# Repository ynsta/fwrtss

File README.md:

fwrtss
======

[FWRTSS](https://www.ynsta.org/fwrtss/doc/html/fwrtss.html) is an open source hardware and software project of a temperature controlled soldering station designed to be used with Weller RT soldering tips.

The majority of the software used to build and debug this project are also open source:

 - KiCad (5126) for PCB design with the [amazing new interactive router from CERN team](http://www.ohwr.org/projects/cern-kicad/wiki/WorkPackages).

 - ARM cross GCC (4.8.3) & binutils,

 - GDB cross, stlink,

 - dfu-util,

 - python, pyside, pyqtgraph,

 - scons, make

 - asciidoc,

 - emacs,

 - ...

The main goal of this project was to teach myself some new stuffs as it is my first real project with a stm32 MCU and also my first surface mount PCB project with 0.5mm pitch components.
Disclaimer

# Warning
 
**A SOLDERING STATION IS A DANGEROUS TOOL**

FWRTSS open source software and hardware are provided "as is" and any express or implied warranties, including, but not limited to, the implied warranties of merchantability and fitness for a particular purpose are disclaimed. in no event shall Stany MARCEL be liable for any direct, indirect, incidental, special, exemplary, or consequential damages (including, but not limited to, procurement of substitute goods or services; loss of use, data, or profits; or business interruption) however caused and on any theory of liability, whether in contract, strict liability, or tort (including negligence or otherwise) arising in any way out of the use of this tool (in whole or in part), even if advised of the possibility of such damage.

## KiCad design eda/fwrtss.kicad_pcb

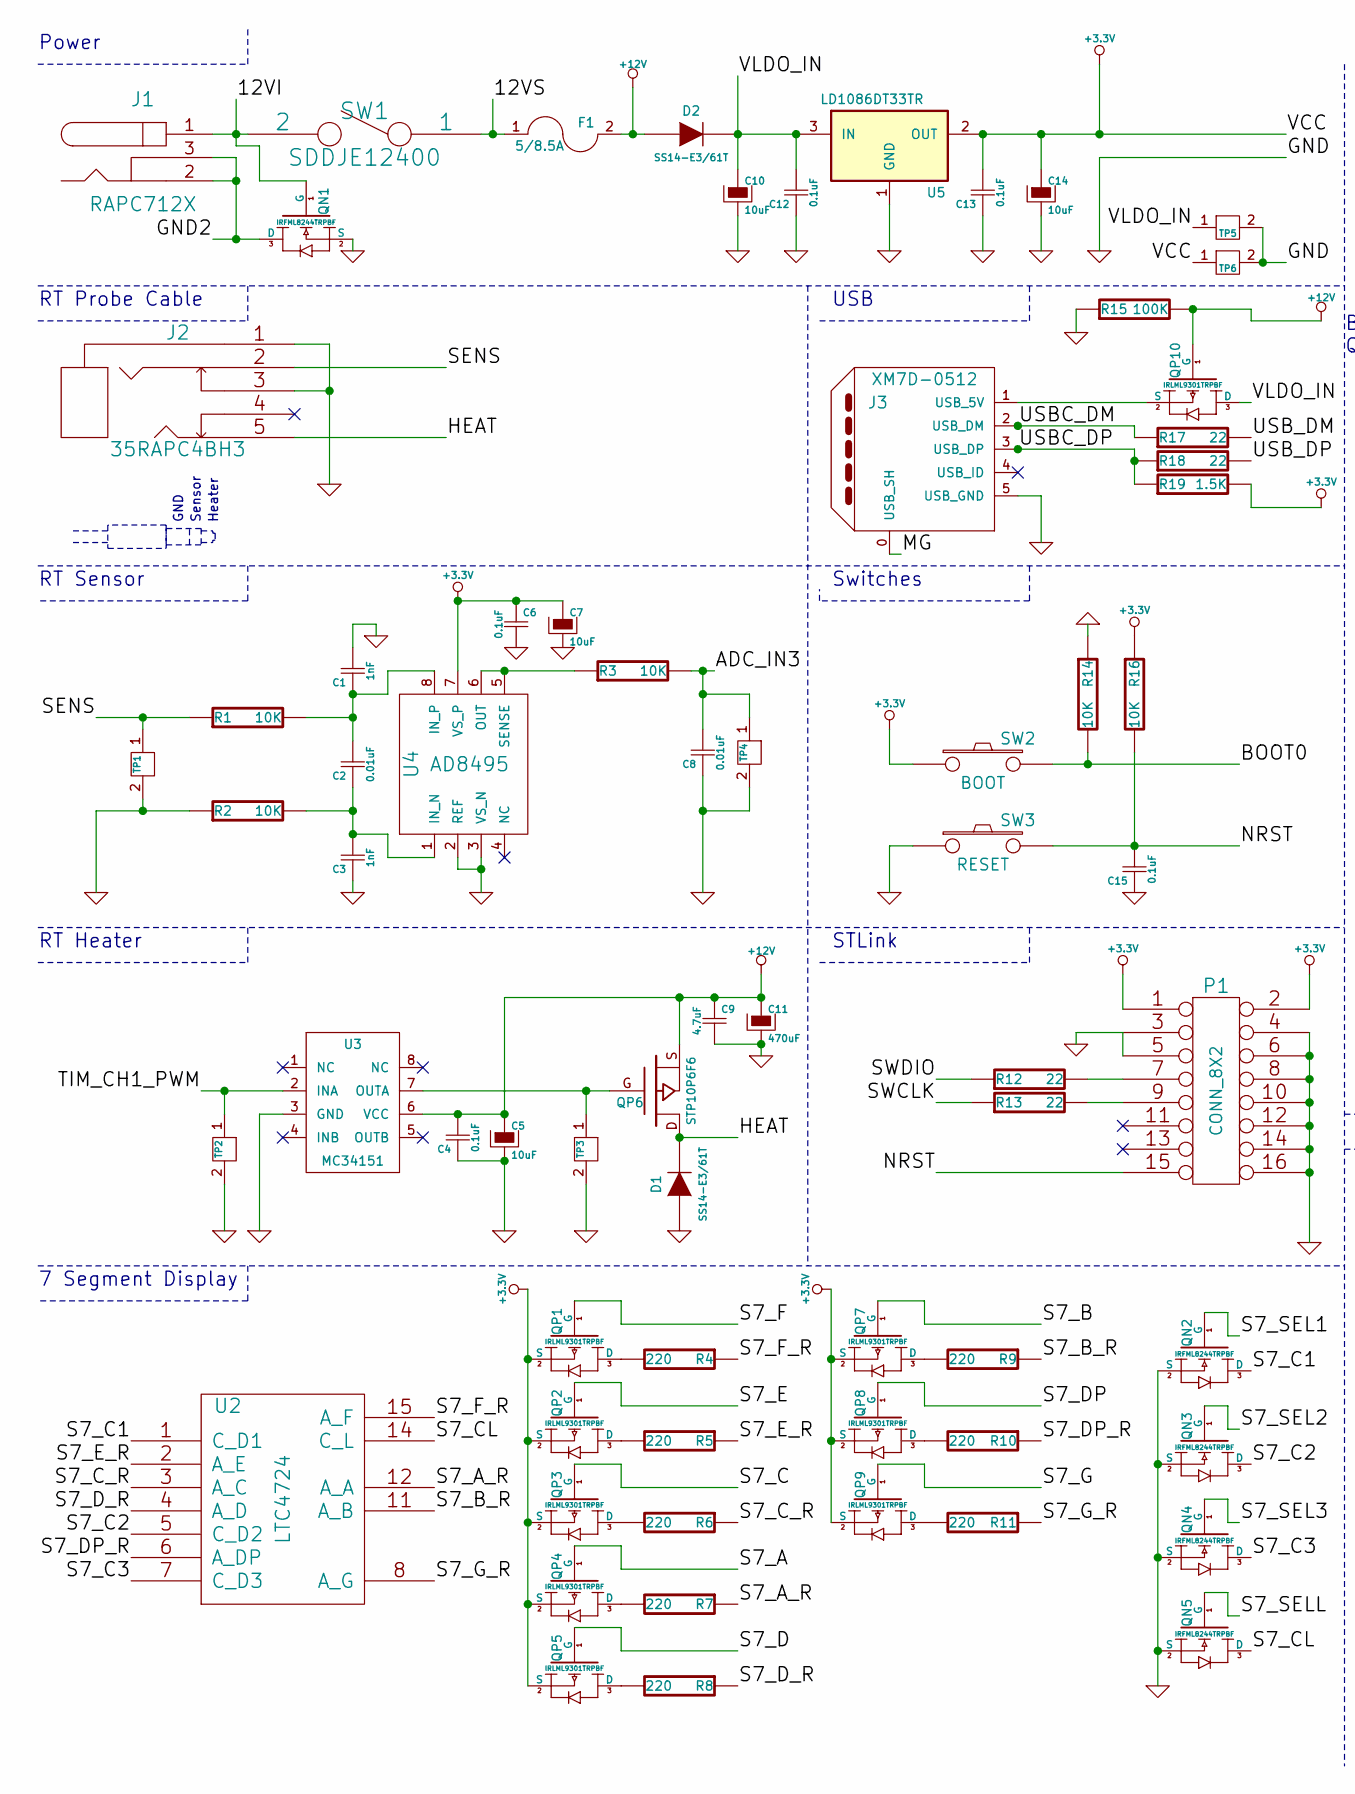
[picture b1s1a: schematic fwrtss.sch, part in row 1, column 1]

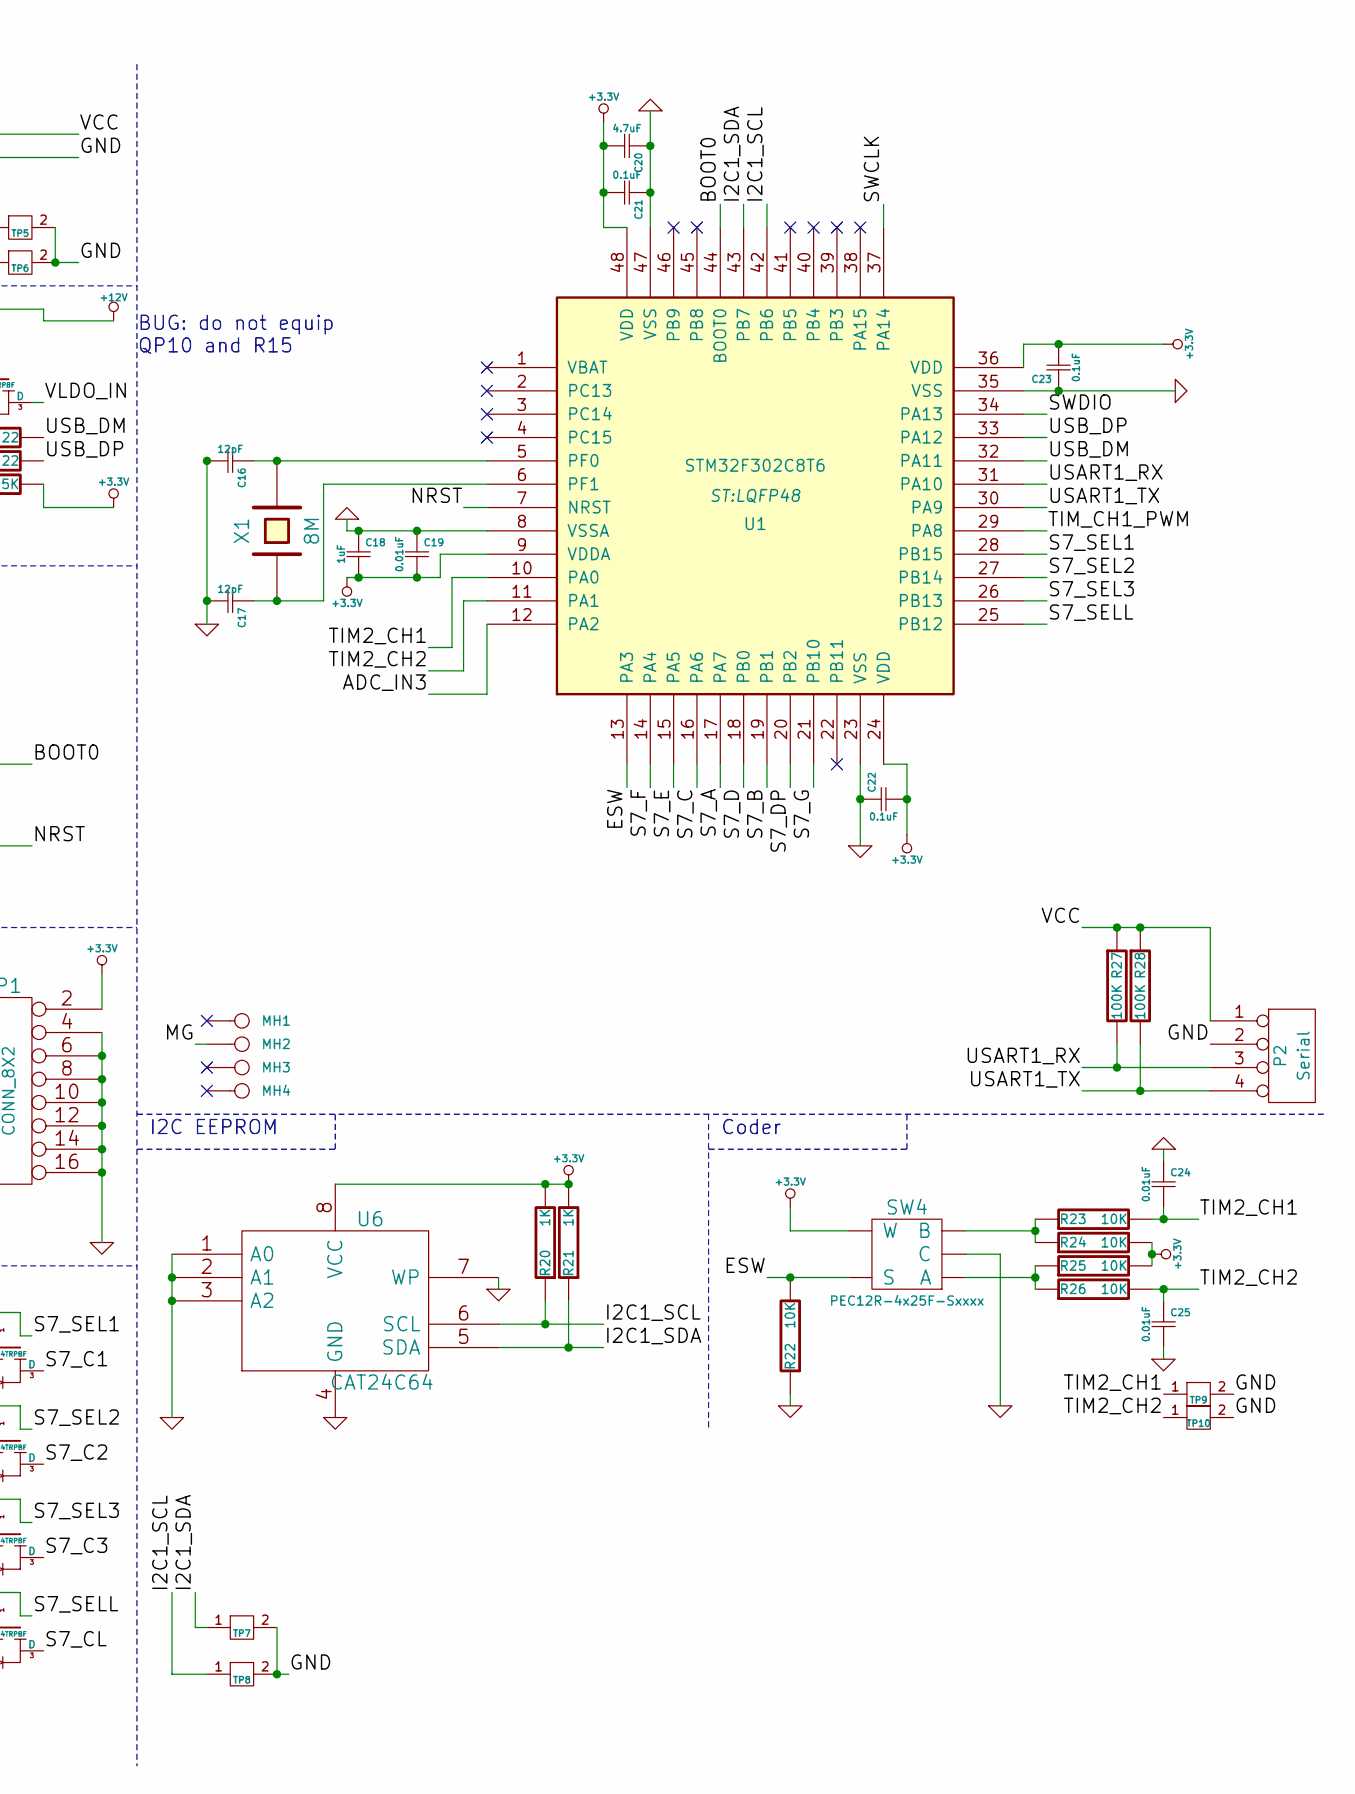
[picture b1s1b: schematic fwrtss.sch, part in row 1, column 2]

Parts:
C1, C3: 1nF; 0805; mouser 81-GCM216R71H102KA7D
C2, C8, C19, C24, C25: 0.01uF; 0805; mouser 81-GRM40Y103Z50D
C4, C6, C12, C13, C15, C21, C22, C23: 0.1uF; 0805; mouser 81-GRM21R71C104MA01J
C5, C7, C10, C14: 10uF; Capacitor5x11RM2.5; mouser 667-EEU-EB1J100SH
C9, C20: 4.7uF; 0805; mouser 81-GRM21BR61E475KA12
C11: 470uF; Capacitor10x21RM5; mouser 647-UPW1E471MPD
C16, C17: 12pF; 0603; mouser 81-GQM1885C1H120JB01
C18: 1uF; 0805; mouser 81-GRM40X105K16L
D1, D2: SS14-E3/61T; DO214AC; mouser 625-SS14-E3
F1: 5/8.5A; Fuse_TE5_Littlefuse-395Series; mouser 650-RGEF500
J1: RAPC712X; RAPC722X; mouser 502-RAPC712X
J2: 35RAPC4BH3; mouser 502-35RAPC4BH3
J3: XM7D-0512; mouser 653-XM7D-0512
MH1, MH2, MH3, MH4: CONN_1; 1pin
P1: CONN_8X2; Pin_Header_Straight_2x08; mouser 649-67996-416HLF
P2: Serial; Pin_Header_Straight_1x04
QN1, QN2, QN3, QN4, QN5: IRFML8244TRPBF; sot23; mouser 942-IRFML8244TRPBF
QP1, QP2, QP3, QP4, QP5, QP7, QP8, QP9, QP10: IRLML9301TRPBF; sot23; mouser 942-IRLML9301TRPBF
QP6: STP10P6F6; TO-220_FET-GDS_Horizontal_LargePads; mouser 511-STP10P6F6
R1, R2, R3, R14, R16, R22, R23, R24, R25, R26: 10K; 0805; mouser 667-ERJ-6ENF1002V
R4, R5, R6, R7, R8, R9, R10, R11: 220; 0805; mouser 667-ERJ-6GEYJ221V
R12, R13, R17, R18: 22; 0805; mouser 667-ERJ-6GEYJ220V
R15, R27, R28: 100K; 0805; mouser 667-ERJ-6GEYJ104V
R19: 1.5K; 0805; mouser 667-ERJ-6GEYJ152V
R20, R21: 1K; 0805; mouser 667-ERJ-6GEYJ102V
SW1: SDDJE12400; mouser 688-SDDJE12400
SW2: BOOT; EVQ2; mouser 667-EVQ-21305R
SW3: RESET; EVQ2; mouser 667-EVQ-21305R
SW4: PEC12R-4x25F-Sxxxx; mouser 652-PEC12R-4225F-S24
TP1, TP2, TP3, TP4, TP5, TP6, TP7, TP8, TP9, TP10: TP2
U1: STM32F302C8T6; LQFP48; mouser 511-STM32F302C8T6
U2: LTC4724; LTC-4724; mouser 859-LTC-4724JR
U3: MC34151; SOIC-8_N; mouser 863-MC34151DR2G
U4: AD8495; MSOP-8; mouser 584-AD8495ARMZ
U5: LD1086DT33TR; DPAK2; mouser 511-LD1086DT33-TR
U6: CAT24C64; SOIC-8_N; mouser 698-CAT24C64WI-G
X1: 8M; X-TH-8.8-dia3.2; mouser 815-AB308-8.000

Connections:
+3.3V: C6.1, C7.1, C13.2, C14.1, C18.2, C19.2, C20.2, C21.2, C22.2, C23.2, P1.1, P1.2, P2.1, QP1.2 (S), QP2.2 (S), QP3.2 (S), QP4.2 (S), QP5.2 (S), QP7.2 (S), QP8.2 (S), QP9.2 (S), R16.1, R19.2, R20.2, R21.2, R24.2, R25.2, R27.1, R28.1, SW2.1, SW4.2 (W), TP6.1, U1.9 (VDDA), U1.24 (VDD), U1.36 (VDD), U1.48 (VDD), U4.7 (VS_P), U5.2 (OUT), U6.8 (VCC)
+12V: C4.2, C5.1, C9.1, C11.1, D2.1 (A), F1.2, QP6.S, QP10.1 (G), R15.2, U3.6 (VCC)
/12VI: J1.1, QN1.1 (G), SW1.2
/12VS: F1.1, SW1.1
/ADC_IN3: C8.2, R3.2, TP4.1, U1.12 (PA2)
/BOOT0: R14.2, SW2.2, U1.44 (BOOT0)
/ESW: R22.2, SW4.1 (S), U1.13 (PA3)
/GND2: J1.2, J1.3, QN1.3 (D)
/HEAT: D1.2 (K), J2.5, QP6.D
/I2C1_SCL: R20.1, TP8.1, U1.42 (PB6), U6.6 (SCL)
/I2C1_SDA: R21.1, TP7.1, U1.43 (PB7), U6.5 (SDA)
/MG: J3.0 (USB_SH), MH2.1
/NRST: C15.2, P1.15, R16.2, SW3.2, U1.7 (NRST)
/S7_A: QP4.1 (G), U1.17 (PA7)
/S7_A_R: R7.1, U2.12 (A_A)
/S7_B: QP7.1 (G), U1.19 (PB1)
/S7_B_R: R9.1, U2.11 (A_B)
/S7_C: QP3.1 (G), U1.16 (PA6)
/S7_C1: QN2.3 (D), U2.1 (C_D1)
/S7_C2: QN3.3 (D), U2.5 (C_D2)
/S7_C3: QN4.3 (D), U2.7 (C_D3)
/S7_CL: QN5.3 (D), U2.14 (C_L)
/S7_C_R: R6.1, U2.3 (A_C)
/S7_D: QP5.1 (G), U1.18 (PB0)
/S7_DP: QP8.1 (G), U1.20 (PB2)
/S7_DP_R: R10.1, U2.6 (A_DP)
/S7_D_R: R8.1, U2.4 (A_D)
/S7_E: QP2.1 (G), U1.15 (PA5)
/S7_E_R: R5.1, U2.2 (A_E)
/S7_F: QP1.1 (G), U1.14 (PA4)
/S7_F_R: R4.1, U2.15 (A_F)
/S7_G: QP9.1 (G), U1.21 (PB10)
/S7_G_R: R11.1, U2.8 (A_G)
/S7_SEL1: QN2.1 (G), U1.28 (PB15)
/S7_SEL2: QN3.1 (G), U1.27 (PB14)
/S7_SEL3: QN4.1 (G), U1.26 (PB13)
/S7_SELL: QN5.1 (G), U1.25 (PB12)
/SENS: J2.2, R1.1, TP1.1
/SWCLK: R13.1, U1.37 (PA14)
/SWDIO: R12.1, U1.34 (PA13)
/TIM2_CH1: C24.2, R23.2, TP9.1, U1.10 (PA0)
/TIM2_CH2: C25.1, R26.2, TP10.1, U1.11 (PA1)
/TIM_CH1_PWM: TP2.1, U1.29 (PA8), U3.2 (INA)
/USART1_RX: P2.3, R27.2, U1.31 (PA10)
/USART1_TX: P2.4, R28.2, U1.30 (PA9)
/USBC_DM: J3.2 (USB_DM), R17.1
/USBC_DP: J3.3 (USB_DP), R18.1, R19.1
/USB_DM: R17.2, U1.32 (PA11)
/USB_DP: R18.2, U1.33 (PA12)
/VLDO_IN: C10.1, C12.2, D2.2 (K), QP10.3 (D), TP5.1, U5.3 (IN)
GND: C1.2, C3.1, C4.1, C5.2, C6.2, C7.2, C8.1, C9.2, C10.2, C11.2, C12.1, C13.1, C14.2, C15.1, C16.2, C17.2, C18.1, C19.1, C20.1, C21.1, C22.1, C23.1, C24.1, C25.2, D1.1 (A), J2.1, J2.3, J3.5 (USB_GND), P1.3, P1.4, P1.5, P1.6, P1.8, P1.10, P1.12, P1.14, P1.16, P2.2, QN1.2 (S), QN2.2 (S), QN3.2 (S), QN4.2 (S), QN5.2 (S), R2.1, R14.1, R15.1, R22.1, SW3.1, SW4.4 (C), TP1.2, TP2.2, TP3.2, TP4.2, TP5.2, TP6.2, TP7.2, TP8.2, TP9.2, TP10.2, U1.8 (VSSA), U1.23 (VSS), U1.35 (VSS), U1.47 (VSS), U3.3 (GND), U4.2 (REF), U4.3 (VS_N), U5.1 (GND), U6.1 (A0), U6.2 (A1), U6.3 (A2), U6.4 (GND), U6.7 (WP)
unnamed: C1.1, C2.2, R1.2, U4.8 (IN_P)
unnamed: C2.1, C3.2, R2.2, U4.1 (IN_N)
unnamed: C16.1, U1.5 (PF0), X1.2
unnamed: C17.1, U1.6 (PF1), X1.1
unnamed: J3.1 (USB_5V), QP10.2 (S)
unnamed: P1.7, R12.2
unnamed: P1.9, R13.2
unnamed: QP1.3 (D), R4.2
unnamed: QP2.3 (D), R5.2
unnamed: QP3.3 (D), R6.2
unnamed: QP4.3 (D), R7.2
unnamed: QP5.3 (D), R8.2
unnamed: QP6.G, TP3.1, U3.7 (OUTA)
unnamed: QP7.3 (D), R9.2
unnamed: QP8.3 (D), R10.2
unnamed: QP9.3 (D), R11.2
unnamed: R3.1, U4.5 (SENSE), U4.6 (OUT)
unnamed: R23.1, R24.1, SW4.3 (B)
unnamed: R25.1, R26.1, SW4.5 (A)

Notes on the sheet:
Heater
Sensor
GND
7 Segment Display
RT Heater
RT Sensor
RT Probe Cable
Power
STLink
Coder
Switches
USB
I2C EEPROM
BUG: do not equip QP10 and R15

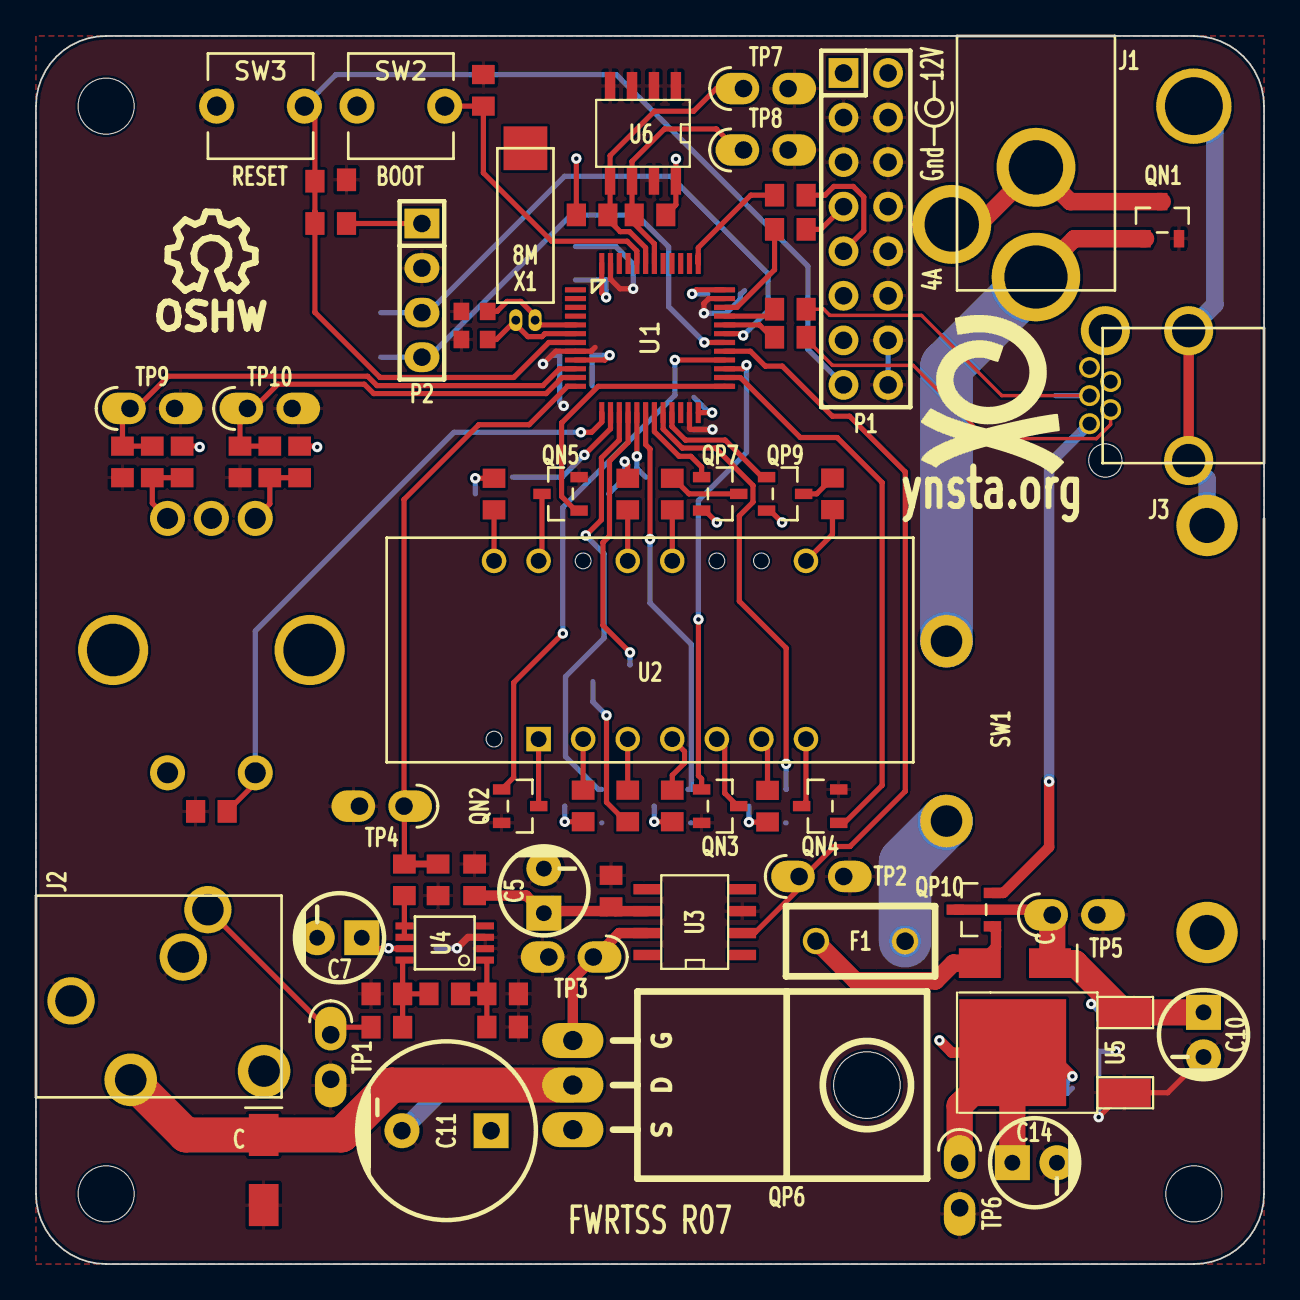
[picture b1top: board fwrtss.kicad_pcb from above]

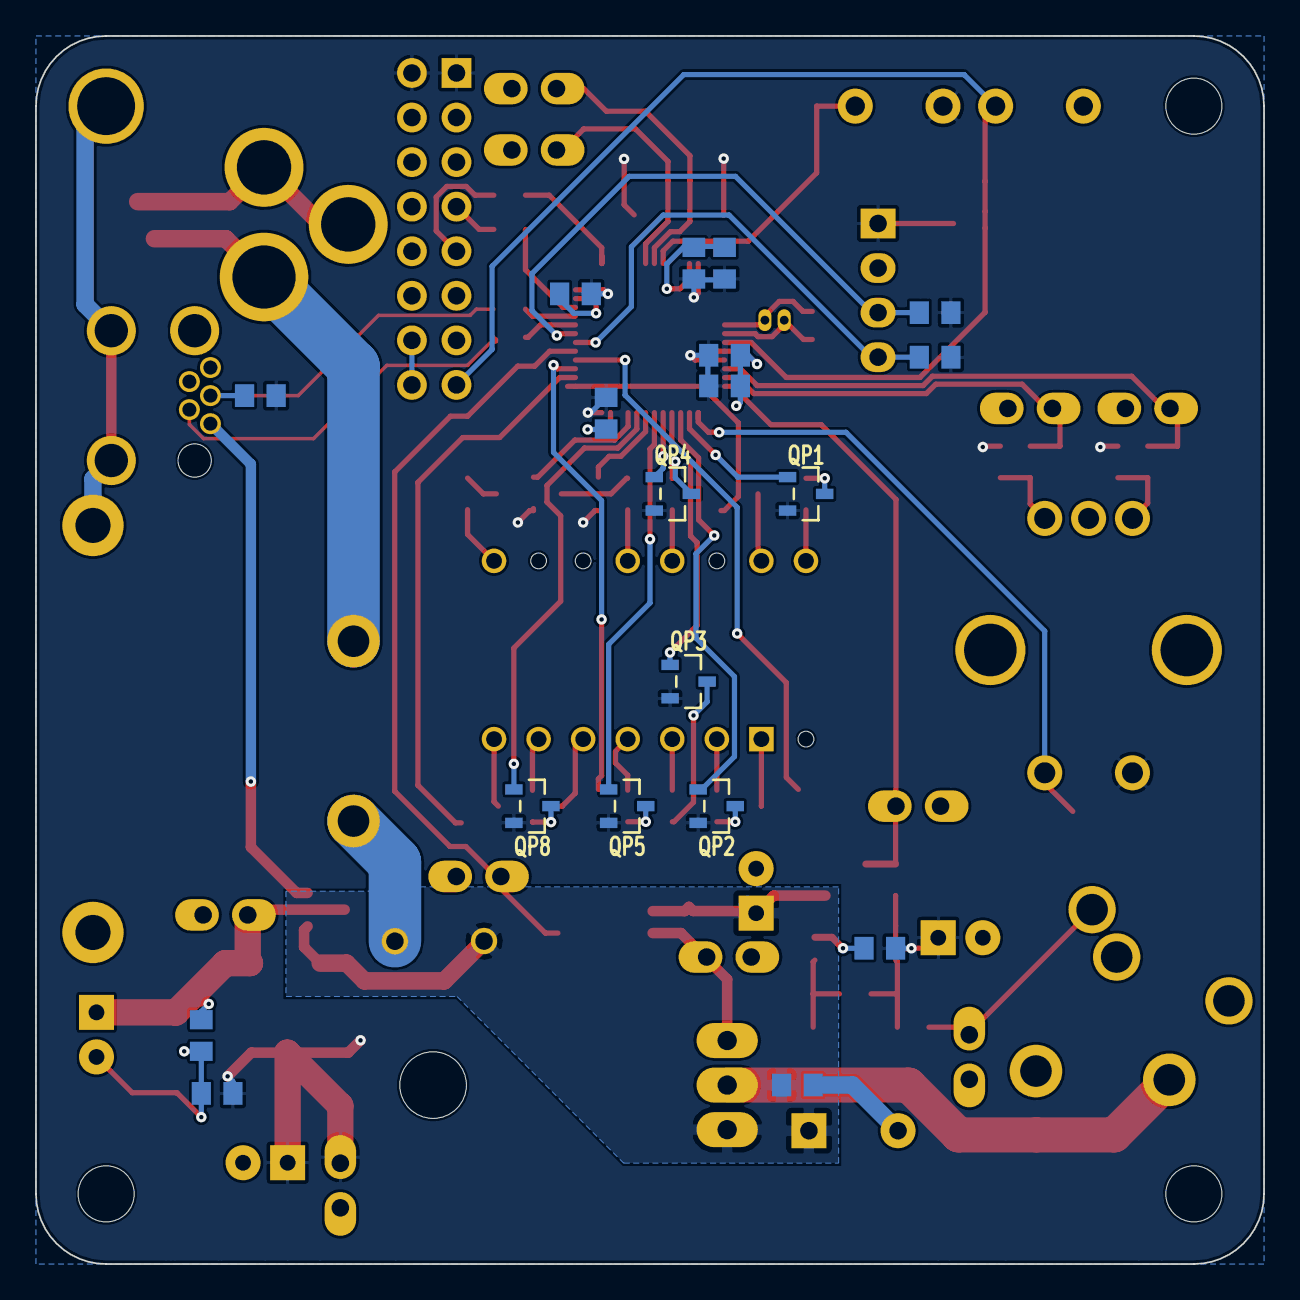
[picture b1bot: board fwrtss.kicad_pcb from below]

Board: 2 copper layers, 70.0 x 70.0 mm, 102 parts (19 on the bottom side), 70 nets.

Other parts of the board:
SYM: Symbol_OSHW-Logo_SilkScreen_07Jul2012; Symbol_OSHW-Logo_SilkScreen

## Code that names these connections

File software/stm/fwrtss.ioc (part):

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Mcu.Name=STM32F302C(6-8)Tx
Mcu.Package=LQFP48
Mcu.UserName=STM32F302C8Tx
PA0.GPIOParameters=GPIO_Label,GPIO_Speed,GPIO_ModeDefaultPP,GPIO_PuPd
PA0.GPIO_Label=ENC_CH1
PA0.GPIO_ModeDefaultPP=GPIO_MODE_AF_PP
PA0.GPIO_PuPd=GPIO_NOPULL
PA0.GPIO_Speed=GPIO_SPEED_LOW
PA0.Signal=S_TIM2_CH1_ETR
PA1.GPIOParameters=GPIO_Label,GPIO_Speed,GPIO_ModeDefaultPP,GPIO_PuPd
PA1.GPIO_Label=ENC_CH2
PA1.GPIO_ModeDefaultPP=GPIO_MODE_AF_PP
PA1.GPIO_PuPd=GPIO_NOPULL
PA1.GPIO_Speed=GPIO_SPEED_LOW
PA1.Signal=S_TIM2_CH2
PA10.GPIOParameters=GPIO_Speed,GPIO_PuPd,GPIO_Mode
PA10.GPIO_Mode=GPIO_MODE_AF_PP
PA10.GPIO_PuPd=GPIO_PULLUP
PA10.GPIO_Speed=GPIO_SPEED_HIGH
PA10.Mode=Asynchronous
PA10.Signal=USART1_RX
PA11.Mode=Device
PA11.Signal=USB_DM
PA12.Mode=Device
PA12.Signal=USB_DP
PA13.Mode=Serial-Wire
PA13.Signal=SYS_JTMS-SWDIO
PA14.Mode=Serial-Wire
PA14.Signal=SYS_JTCK-SWCLK
PA15.Signal=GPIO_Analog
PA2.GPIOParameters=GPIO_Label,GPIO_PuPd,GPIO_Mode
PA2.GPIO_Label=SENS_IN
PA2.GPIO_Mode=GPIO_MODE_ANALOG
PA2.GPIO_PuPd=GPIO_NOPULL
PA2.Mode=IN3-Single-Ended
PA2.Signal=ADC1_IN3
PA3.Signal=S_TIM15_CH2
PA4.GPIOParameters=GPIO_ModeDefaultOutputPP,GPIO_Label,GPIO_Speed,GPIO_PuPd
PA4.GPIO_Label=S7_F
PA4.GPIO_ModeDefaultOutputPP=GPIO_MODE_OUTPUT_PP
PA4.GPIO_PuPd=GPIO_NOPULL
PA4.GPIO_Speed=GPIO_SPEED_LOW
PA4.Signal=GPIO_Output
PA5.GPIOParameters=GPIO_ModeDefaultOutputPP,GPIO_Label,GPIO_Speed,GPIO_PuPd
PA5.GPIO_Label=S7_E
PA5.GPIO_ModeDefaultOutputPP=GPIO_MODE_OUTPUT_PP
PA5.GPIO_PuPd=GPIO_NOPULL
PA5.GPIO_Speed=GPIO_SPEED_LOW
PA5.Signal=GPIO_Output
PA6.GPIOParameters=GPIO_ModeDefaultOutputPP,GPIO_Label,GPIO_Speed,GPIO_PuPd
PA6.GPIO_Label=S7_C
PA6.GPIO_ModeDefaultOutputPP=GPIO_MODE_OUTPUT_PP
PA6.GPIO_PuPd=GPIO_NOPULL
PA6.GPIO_Speed=GPIO_SPEED_LOW
PA6.Signal=GPIO_Output
PA7.GPIOParameters=GPIO_ModeDefaultOutputPP,GPIO_Label,GPIO_Speed,GPIO_PuPd
PA7.GPIO_Label=S7_A
PA7.GPIO_ModeDefaultOutputPP=GPIO_MODE_OUTPUT_PP
PA7.GPIO_PuPd=GPIO_NOPULL
PA7.GPIO_Speed=GPIO_SPEED_LOW
PA7.Signal=GPIO_Output
PA8.GPIOParameters=GPIO_Label,GPIO_Speed,GPIO_ModeDefaultPP,GPIO_PuPd
PA8.GPIO_Label=PWM_OUT
PA8.GPIO_ModeDefaultPP=GPIO_MODE_AF_PP
PA8.GPIO_PuPd=GPIO_NOPULL
PA8.GPIO_Speed=GPIO_SPEED_HIGH
PA8.Signal=S_TIM1_CH1
PA9.GPIOParameters=GPIO_Speed,GPIO_PuPd,GPIO_Mode
PA9.GPIO_Mode=GPIO_MODE_AF_PP
PA9.GPIO_PuPd=GPIO_PULLUP
PA9.GPIO_Speed=GPIO_SPEED_HIGH
PA9.Mode=Asynchronous
PA9.Signal=USART1_TX
PB0.GPIOParameters=GPIO_ModeDefaultOutputPP,GPIO_Label,GPIO_Speed,GPIO_PuPd
PB0.GPIO_Label=S7_D
PB0.GPIO_ModeDefaultOutputPP=GPIO_MODE_OUTPUT_PP
PB0.GPIO_PuPd=GPIO_NOPULL
PB0.GPIO_Speed=GPIO_SPEED_LOW
PB0.Signal=GPIO_Output
PB1.GPIOParameters=GPIO_ModeDefaultOutputPP,GPIO_Label,GPIO_Speed,GPIO_PuPd
PB1.GPIO_Label=S7_B
PB1.GPIO_ModeDefaultOutputPP=GPIO_MODE_OUTPUT_PP
PB1.GPIO_PuPd=GPIO_NOPULL
PB1.GPIO_Speed=GPIO_SPEED_LOW
PB1.Signal=GPIO_Output
PB10.GPIOParameters=GPIO_ModeDefaultOutputPP,GPIO_Label,GPIO_Speed,GPIO_PuPd
PB10.GPIO_Label=S7_G
PB10.GPIO_ModeDefaultOutputPP=GPIO_MODE_OUTPUT_PP
PB10.GPIO_PuPd=GPIO_NOPULL
PB10.GPIO_Speed=GPIO_SPEED_LOW
PB10.Signal=GPIO_Output
PB11.Signal=GPIO_Analog
PB12.GPIOParameters=GPIO_ModeDefaultOutputPP,GPIO_Label,GPIO_Speed,GPIO_PuPd
PB12.GPIO_Label=S7_SELL
PB12.GPIO_ModeDefaultOutputPP=GPIO_MODE_OUTPUT_PP
PB12.GPIO_PuPd=GPIO_NOPULL
PB12.GPIO_Speed=GPIO_SPEED_LOW
PB12.Signal=GPIO_Output
PB13.GPIOParameters=GPIO_ModeDefaultOutputPP,GPIO_Label,GPIO_Speed,GPIO_PuPd
PB13.GPIO_Label=S7_SEL3
PB13.GPIO_ModeDefaultOutputPP=GPIO_MODE_OUTPUT_PP
PB13.GPIO_PuPd=GPIO_NOPULL
PB13.GPIO_Speed=GPIO_SPEED_LOW
PB13.Signal=GPIO_Output
PB14.GPIOParameters=GPIO_ModeDefaultOutputPP,GPIO_Label,GPIO_Speed,GPIO_PuPd
PB14.GPIO_Label=S7_SEL2
PB14.GPIO_ModeDefaultOutputPP=GPIO_MODE_OUTPUT_PP
PB14.GPIO_PuPd=GPIO_NOPULL
PB14.GPIO_Speed=GPIO_SPEED_LOW
PB14.Signal=GPIO_Output
PB15.GPIOParameters=GPIO_ModeDefaultOutputPP,GPIO_Label,GPIO_Speed,GPIO_PuPd
PB15.GPIO_Label=S7_SEL1
PB15.GPIO_ModeDefaultOutputPP=GPIO_MODE_OUTPUT_PP
PB15.GPIO_PuPd=GPIO_NOPULL
PB15.GPIO_Speed=GPIO_SPEED_LOW
PB15.Signal=GPIO_Output
PB2.GPIOParameters=GPIO_ModeDefaultOutputPP,GPIO_Label,GPIO_Speed,GPIO_PuPd
PB2.GPIO_Label=S7_DP
PB2.GPIO_ModeDefaultOutputPP=GPIO_MODE_OUTPUT_PP
PB2.GPIO_PuPd=GPIO_NOPULL
PB2.GPIO_Speed=GPIO_SPEED_LOW
PB2.Signal=GPIO_Output
PB3.Signal=GPIO_Analog
PB4.Signal=GPIO_Analog
PB5.Signal=GPIO_Analog
PB6.GPIOParameters=GPIO_FM6,GPIO_Speed,GPIO_PuPd,GPIO_Mode
PB6.GPIO_FM6=__NULL
PB6.GPIO_Mode=GPIO_MODE_AF_OD
PB6.GPIO_PuPd=GPIO_NOPULL
PB6.GPIO_Speed=GPIO_SPEED_HIGH
PB6.Mode=I2C
PB6.Signal=I2C1_SCL
PB7.GPIOParameters=GPIO_FM6,GPIO_Speed,GPIO_PuPd,GPIO_Mode
PB7.GPIO_FM6=__NULL
PB7.GPIO_Mode=GPIO_MODE_AF_OD
PB7.GPIO_PuPd=GPIO_NOPULL
PB7.GPIO_Speed=GPIO_SPEED_HIGH
PB7.Mode=I2C
PB7.Signal=I2C1_SDA
PB8.Signal=GPIO_Analog
PB9.Signal=GPIO_Analog
PC13.Signal=GPIO_Analog
PC14\ -\ OSC32_IN.Signal=GPIO_Analog
PC15\ -\ OSC32_OUT.Signal=GPIO_Analog
PF0-OSC_IN.Mode=HSE-External-Oscillator
PF0-OSC_IN.Signal=RCC_OSC_IN
PF1-OSC_OUT.Mode=HSE-External-Oscillator
PF1-OSC_OUT.Signal=RCC_OSC_OUT
RCC.HSE_VALUE=8000000
RCC.SYSCLKSource=RCC_SYSCLKSOURCE_PLLCLK

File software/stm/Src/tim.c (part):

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    __TIM1_CLK_ENABLE();

    /**TIM1 GPIO Configuration
    PA8     ------> TIM1_CH1
    */
    GPIO_InitStruct.Pin = GPIO_PIN_8;
    GPIO_InitStruct.Mode = GPIO_MODE_AF_PP;
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    __TIM2_CLK_ENABLE();

    /**TIM2 GPIO Configuration
    PA0     ------> TIM2_CH1
    PA1     ------> TIM2_CH2
    */
    GPIO_InitStruct.Pin = GPIO_PIN_0|GPIO_PIN_1;
    GPIO_InitStruct.Mode = GPIO_MODE_AF_PP;
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    __TIM15_CLK_ENABLE();

    /**TIM15 GPIO Configuration
    PA3     ------> TIM15_CH2
    */
    GPIO_InitStruct.Pin = GPIO_PIN_3;
    GPIO_InitStruct.Mode = GPIO_MODE_AF_PP;
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    __TIM1_CLK_DISABLE();

    /**TIM1 GPIO Configuration
    PA8     ------> TIM1_CH1
    */
    HAL_GPIO_DeInit(GPIOA, GPIO_PIN_8);

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    __TIM2_CLK_DISABLE();

    /**TIM2 GPIO Configuration
    PA0     ------> TIM2_CH1
    PA1     ------> TIM2_CH2
    */
    HAL_GPIO_DeInit(GPIOA, GPIO_PIN_0|GPIO_PIN_1);

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    __TIM15_CLK_DISABLE();

    /**TIM15 GPIO Configuration
    PA3     ------> TIM15_CH2
    */
    HAL_GPIO_DeInit(GPIOA, GPIO_PIN_3);

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
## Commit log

2014-09-15 Create from private commit 1e99ea710
2014-09-15 Add a project README
2014-09-15 Remove Introduction title
2014-09-16 SCH R07.1

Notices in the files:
software/stm/Src/tim.c:
COPYRIGHT(c) 2014 STMicroelectronics
(C) COPYRIGHT STMicroelectronics *****END OF FILE
eda/fwrtss.kicad_pcb:
Stany MARCEL (c) 2014
